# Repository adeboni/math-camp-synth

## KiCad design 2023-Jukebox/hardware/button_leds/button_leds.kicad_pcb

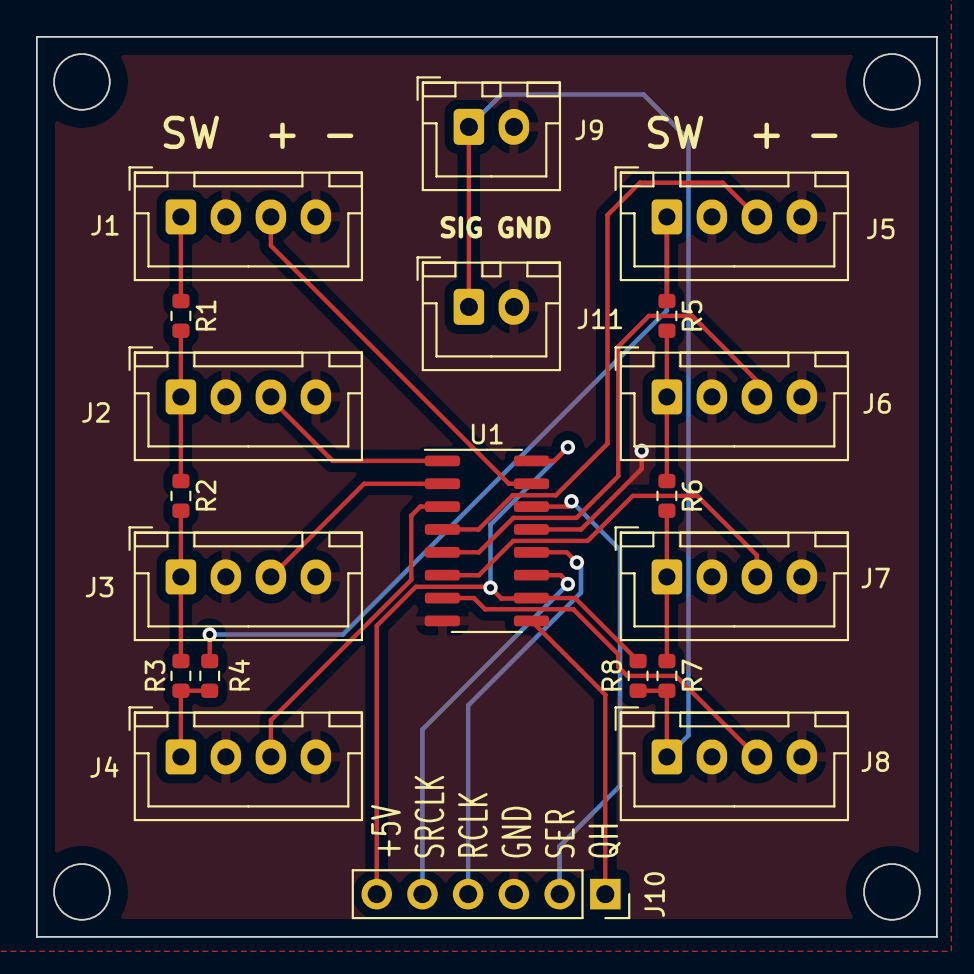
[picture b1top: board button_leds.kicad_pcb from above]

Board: 2 copper layers, 50.0 x 50.0 mm, 20 parts (0 on the bottom side), 22 nets.

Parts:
J1, J2, J3, J4, J5, J6, J7, J8: Conn_01x04; JST_XH_B4B-XH-A_1x04_P2.50mm_Vertical
J9, J11: JST_XH; JST_XH_B2B-XH-A_1x02_P2.50mm_Vertical
J10: Conn_01x06; PinSocket_1x06_P2.54mm_Vertical
R1, R2, R3, R4, R5, R6, R7, R8: 1k; R_0603_1608Metric
U1: 74HC595; SOIC-16_3.9x9.9mm_P1.27mm

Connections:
+5V: J10.6, R8.2, U1.10 (~SRCLR), U1.16 (VCC)
A1: J8.1, J9.1, J11.1, R7.2, R8.1
B1: J1.3, U1.15 (QA)
B2: J2.3, U1.1 (QB)
B3: J3.3, U1.2 (QC)
B4: J4.3, U1.3 (QD)
B5: J5.3, U1.4 (QE)
B6: J6.3, U1.5 (QF)
B7: J7.3, U1.6 (QG)
B8: J8.3, U1.7 (QH)
GND: J1.2, J1.4, J2.2, J2.4, J3.2, J3.4, J4.2, J4.4, J5.2, J5.4, J6.2, J6.4, J7.2, J7.4, J8.2, J8.4, J9.2, J10.3, J11.2, U1.8 (GND), U1.13 (~OE)
unnamed: J1.1, R1.1
unnamed: J2.1, R1.2, R2.1
unnamed: J3.1, R2.2, R3.1
unnamed: J4.1, R3.2, R4.1
unnamed: J5.1, R4.2, R5.1
unnamed: J6.1, R5.2, R6.1
unnamed: J7.1, R6.2, R7.1
QH: J10.1, U1.9 (QH')
RCLK: J10.4, U1.12 (RCLK)
SER: J10.2, U1.14 (SER)
SRCLK: J10.5, U1.11 (SRCLK)

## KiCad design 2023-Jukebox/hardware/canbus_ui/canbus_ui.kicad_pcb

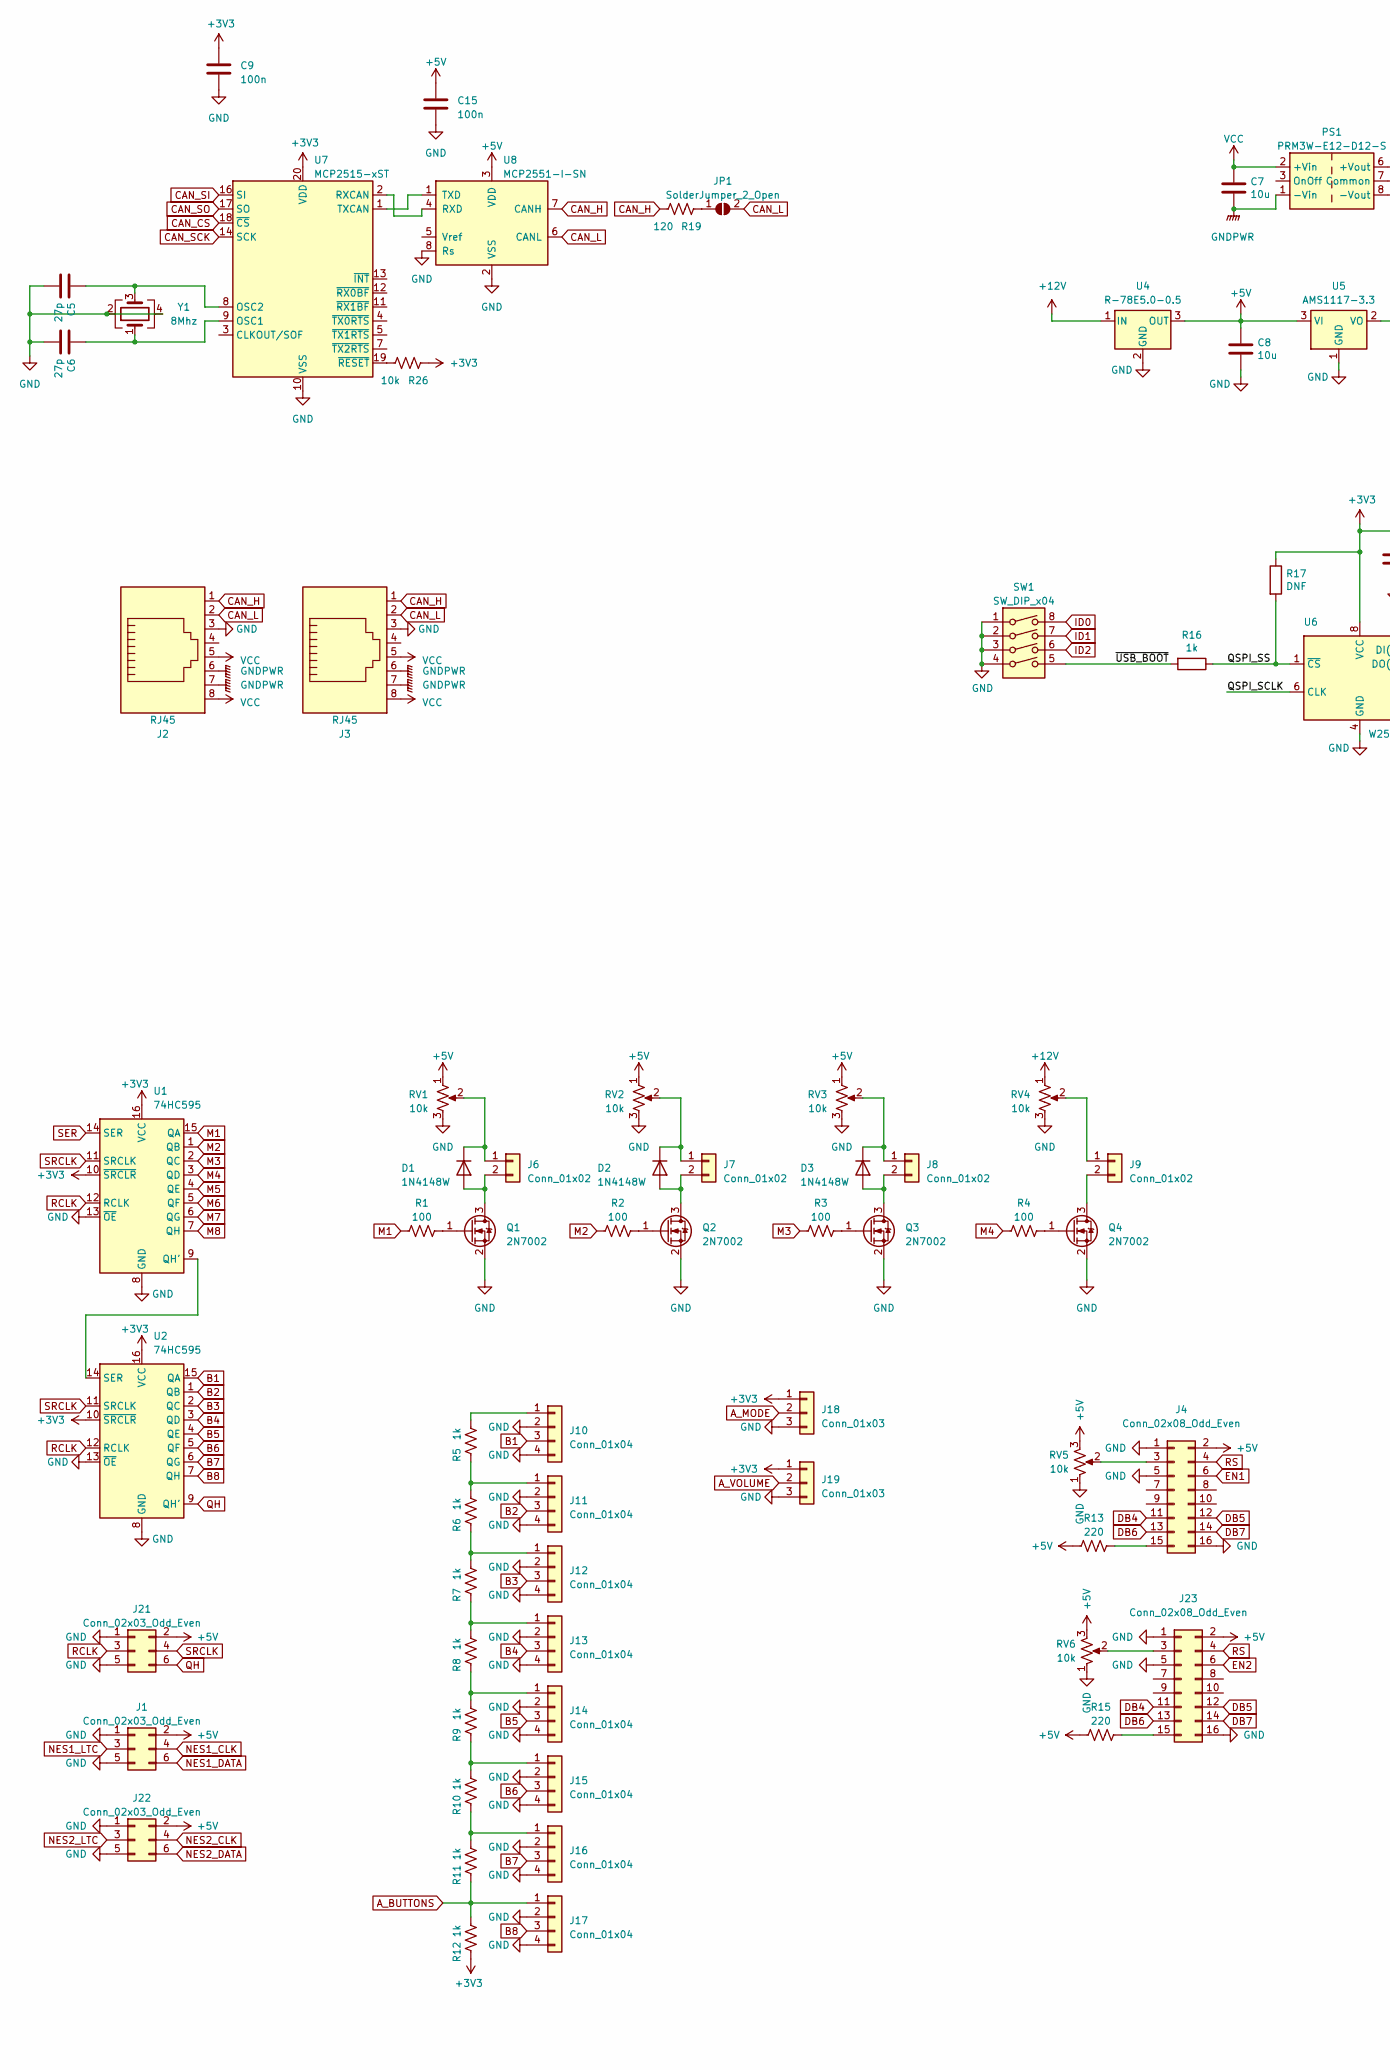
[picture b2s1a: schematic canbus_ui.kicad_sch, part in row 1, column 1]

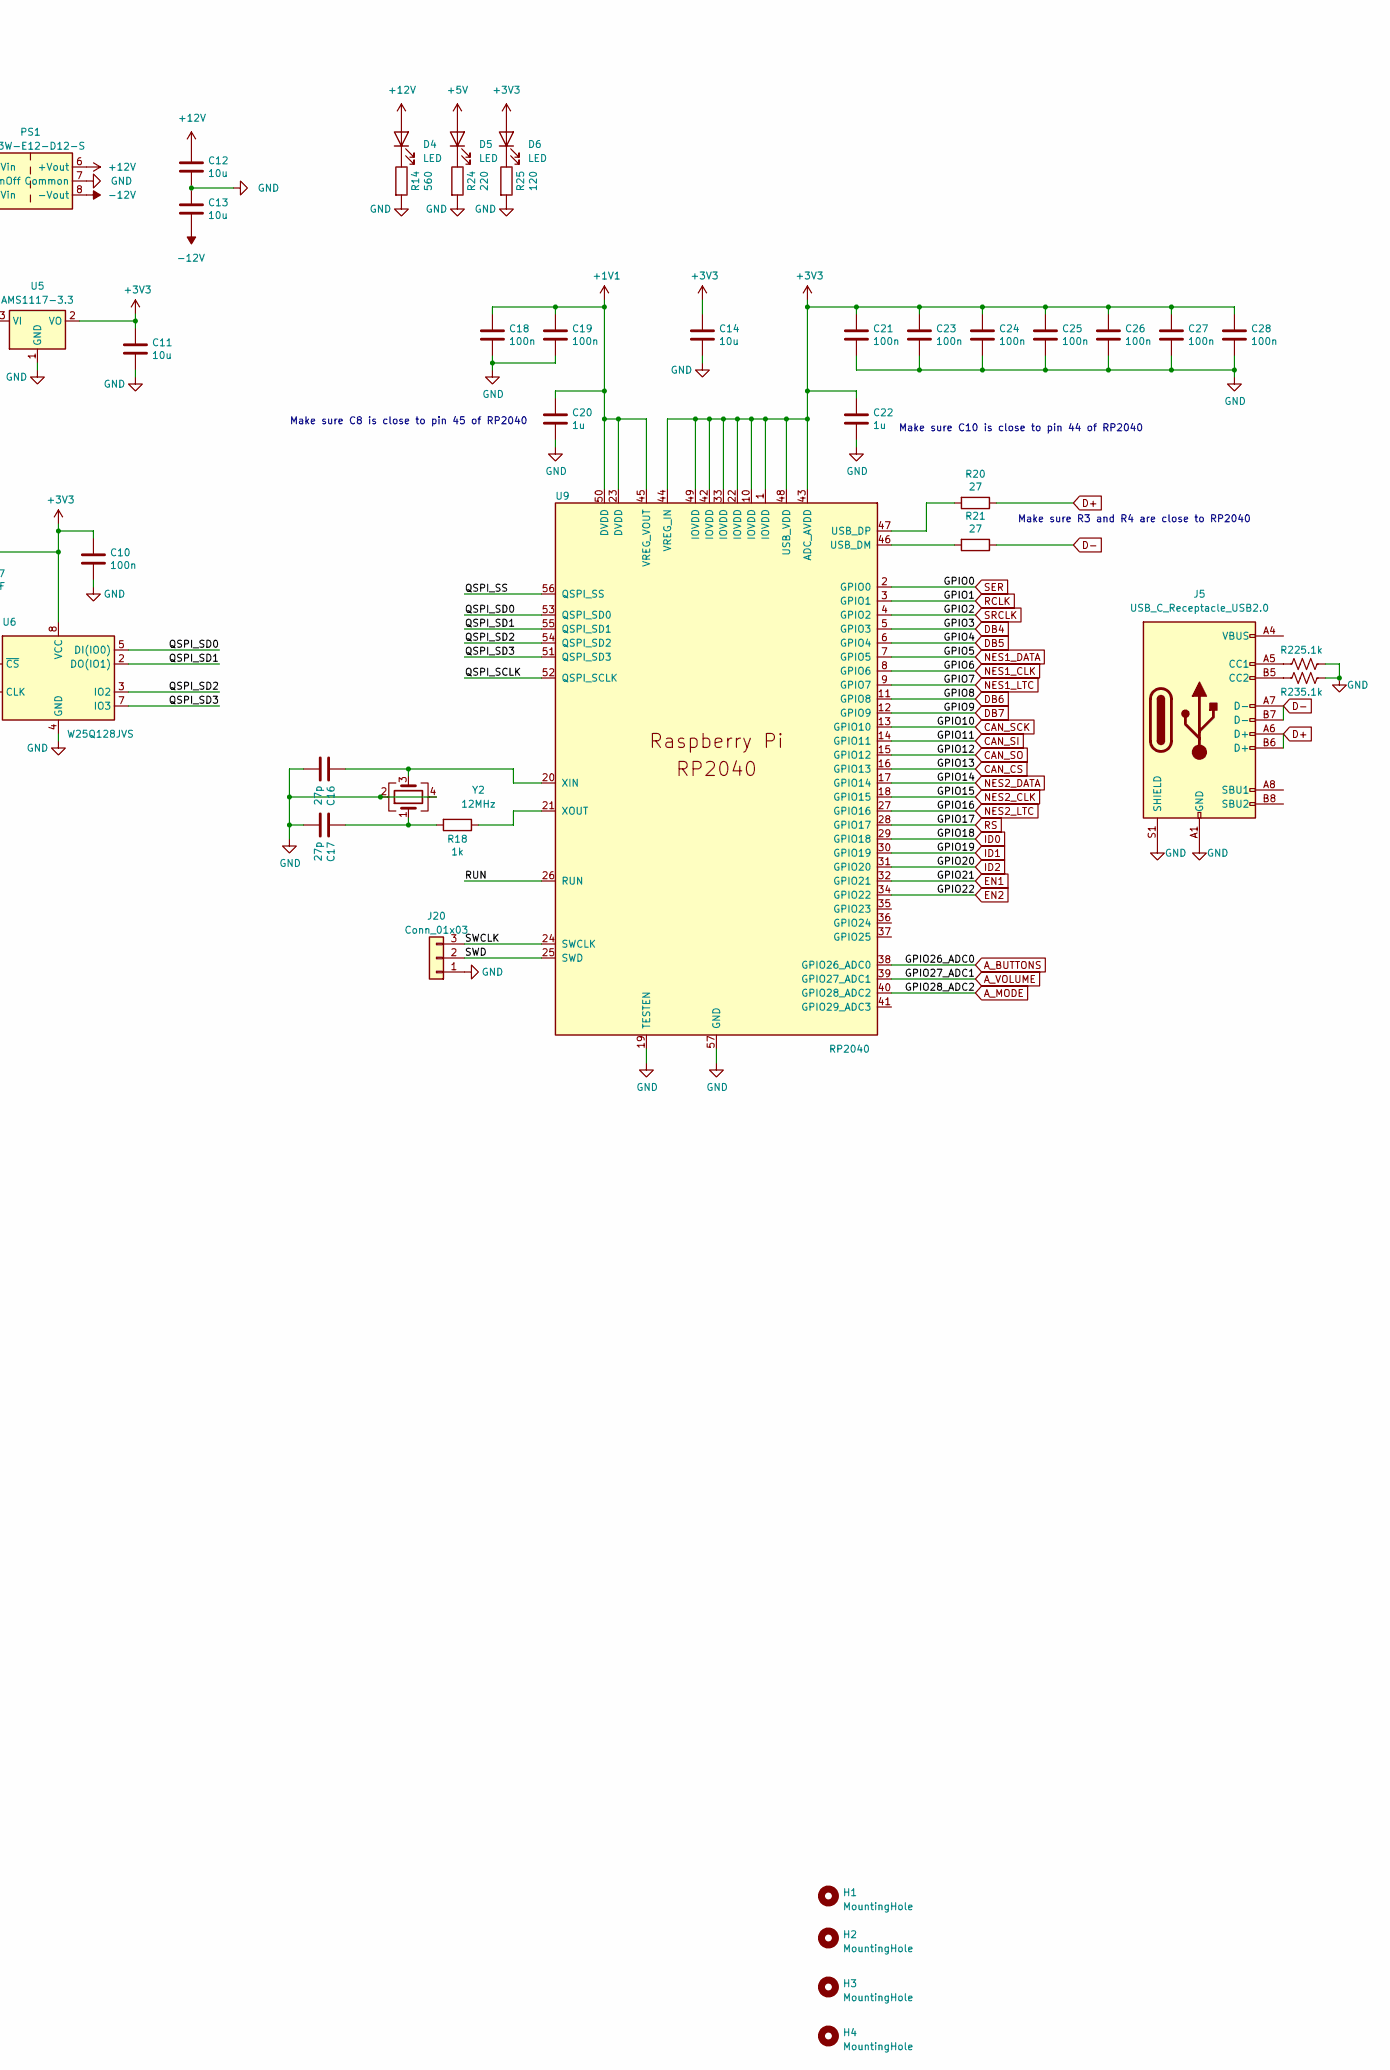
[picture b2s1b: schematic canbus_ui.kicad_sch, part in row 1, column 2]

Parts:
C5, C6, C16, C17: 27p; C_0603_1608Metric
C7, C8, C11, C12, C13, C14: 10u; C_0603_1608Metric
C9, C10, C15, C18, C19, C21, C23, C24, C25, C26, C27, C28: 100n; C_0603_1608Metric
C20, C22: 1u; C_0603_1608Metric
D1, D2, D3: 1N4148W; D_SOD-123
D4, D5, D6: LED; LED_0603_1608Metric
H1, H2, H3, H4: MountingHole; MountingHole_3.2mm_M3
J1, J21, J22: Conn_02x03_Odd_Even; IDC-Header_2x03_P2.54mm_Vertical
J2, J3: RJ45; RJ45_Amphenol_54602-x08_Horizontal
J4, J23: Conn_02x08_Odd_Even; IDC-Header_2x08_P2.54mm_Vertical
J5: USB_C_Receptacle_USB2.0; USB_C_Receptacle_Palconn_UTC16-G
J6, J7, J8, J9: Conn_01x02; JST_XH_B2B-XH-A_1x02_P2.50mm_Vertical
J10, J11, J12, J13, J14, J15, J16, J17: Conn_01x04; JST_XH_B4B-XH-A_1x04_P2.50mm_Vertical
J18, J19: Conn_01x03; JST_XH_B3B-XH-A_1x03_P2.50mm_Vertical
J20: Conn_01x03; PinHeader_1x03_P2.54mm_Vertical
JP1: SolderJumper_2_Open; SolderJumper-2_P1.3mm_Open_RoundedPad1.0x1.5mm
PS1: PRM3W-E12-D12-S; Converter_DCDC_XP_POWER-ITxxxxxS_THT
Q1, Q2, Q3, Q4: 2N7002; SOT-23
R1, R2, R3, R4: 100; R_0603_1608Metric
R5, R6, R7, R8, R9, R10, R11, R12, R16, R18: 1k; R_0603_1608Metric
R13, R15, R24: 220; R_0603_1608Metric
R14: 560; R_0603_1608Metric
R17: DNF; R_0603_1608Metric
R19, R25: 120; R_0603_1608Metric
R20, R21: 27; R_0603_1608Metric
R22, R23: 5.1k; R_0603_1608Metric
R26: 10k; R_0603_1608Metric
RV1, RV2, RV3, RV4, RV5, RV6: 10k; Potentiometer_Bourns_3386P_Vertical
SW1: SW_DIP_x04; SW_DIP_SPSTx04_Slide_Omron_A6S-410x_W8.9mm_P2.54mm
U1, U2: 74HC595; SOIC-16_3.9x9.9mm_P1.27mm
U4: R-78E5.0-0.5; Converter_DCDC_RECOM_R-78E-0.5_THT
U5: AMS1117-3.3; SOT-223-3_TabPin2
U6: W25Q128JVS; SOIC-8_5.23x5.23mm_P1.27mm
U7: MCP2515-xST; TSSOP-20_4.4x6.5mm_P0.65mm
U8: MCP2551-I-SN; SOIC-8_3.9x4.9mm_P1.27mm
U9: RP2040; QFN-56-1EP_7x7mm_P0.4mm_EP3.2x3.2mm
Y1: 8Mhz; Crystal_SMD_3225-4Pin_3.2x2.5mm
Y2: 12MHz; Crystal_SMD_3225-4Pin_3.2x2.5mm

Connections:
+1V1: C18.1, C19.1, C20.1, U9.23 (DVDD), U9.45 (VREG_VOUT), U9.50 (DVDD)
+3V3: C9.1, C10.1, C11.1, C14.1, C21.1, C22.1, C23.1, C24.1, C25.1, C26.1, C27.1, C28.1, D6.2 (A), J18.1, J19.1, R12.2, R17.1, R26.1, U1.10 (~SRCLR), U1.16 (VCC), U2.10 (~SRCLR), U2.16 (VCC), U5.2 (VO), U6.8 (VCC), U7.20 (VDD), U9.1 (IOVDD), U9.10 (IOVDD), U9.22 (IOVDD), U9.33 (IOVDD), U9.42 (IOVDD), U9.43 (ADC_AVDD), U9.44 (VREG_IN), U9.48 (USB_VDD), U9.49 (IOVDD)
+5V: C8.1, C15.1, D5.2 (A), J1.2, J4.2, J21.2, J22.2, J23.2, R13.1, R15.1, RV1.1, RV2.1, RV3.1, RV5.3, RV6.3, U4.3 (OUT), U5.3 (VI), U8.3 (VDD)
+12V: C12.1, D4.2 (A), PS1.6 (+Vout), RV4.1, U4.1 (IN)
-12V: C13.2, PS1.8 (-Vout)
/QSPI_SCLK: U6.6 (CLK), U9.52 (QSPI_SCLK)
/QSPI_SD0: U6.5 (DI(IO0)), U9.53 (QSPI_SD0)
/QSPI_SD1: U6.2 (DO(IO1)), U9.55 (QSPI_SD1)
/QSPI_SD2: U6.3 (IO2), U9.54 (QSPI_SD2)
/QSPI_SD3: U6.7 (IO3), U9.51 (QSPI_SD3)
/QSPI_SS: R16.1, R17.2, U6.1 (~CS), U9.56 (QSPI_SS)
/RUN: U9.26 (RUN)
/SWCLK: J20.3, U9.24 (SWCLK)
/SWD: J20.2, U9.25 (SWD)
/~USB_BOOT: R16.2, SW1.5
A_BUTTONS: J17.1, R11.2, R12.1, U9.38 (GPIO26_ADC0)
A_MODE: J18.2, U9.40 (GPIO28_ADC2)
A_VOLUME: J19.2, U9.39 (GPIO27_ADC1)
B1: J10.3, U2.15 (QA)
B2: J11.3, U2.1 (QB)
B3: J12.3, U2.2 (QC)
B4: J13.3, U2.3 (QD)
B5: J14.3, U2.4 (QE)
B6: J15.3, U2.5 (QF)
B7: J16.3, U2.6 (QG)
B8: J17.3, U2.7 (QH)
CAN_CS: U7.18 (~CS), U9.16 (GPIO13)
CAN_H: J2.1, J3.1, R19.2, U8.7 (CANH)
CAN_L: J2.2, J3.2, JP1.2 (B), U8.6 (CANL)
CAN_SCK: U7.14 (SCK), U9.13 (GPIO10)
CAN_SI: U7.16 (SI), U9.14 (GPIO11)
CAN_SO: U7.17 (SO), U9.15 (GPIO12)
D+: J5.A6 (D+), J5.B6 (D+), R20.1
D-: J5.A7 (D-), J5.B7 (D-), R21.1
DB4: J4.11, J23.11, U9.5 (GPIO3)
DB5: J4.12, J23.12, U9.6 (GPIO4)
DB6: J4.13, J23.13, U9.11 (GPIO8)
DB7: J4.14, J23.14, U9.12 (GPIO9)
EN1: J4.6, U9.32 (GPIO21)
EN2: J23.6, U9.34 (GPIO22)
GND: C5.2, C6.2, C8.2, C9.2, C10.2, C11.2, C12.2, C13.1, C14.2, C15.2, C16.2, C17.2, C18.2, C19.2, C20.2, C21.2, C22.2, C23.2, C24.2, C25.2, C26.2, C27.2, C28.2, J1.1, J1.5, J2.3, J3.3, J4.1, J4.5, J4.16, J5.A1 (GND), J5.A12 (GND), J5.B1 (GND), J5.B12 (GND), J5.S1 (SHIELD), J10.2, J10.4, J11.2, J11.4, J12.2, J12.4, J13.2, J13.4, J14.2, J14.4, J15.2, J15.4, J16.2, J16.4, J17.2, J17.4, J18.3, J19.3, J20.1, J21.1, J21.5, J22.1, J22.5, J23.1, J23.5, J23.16, PS1.7 (Common), Q1.2 (S), Q2.2 (S), Q3.2 (S), Q4.2 (S), R14.2, R22.1, R23.1, R24.2, R25.2, RV1.3, RV2.3, RV3.3, RV4.3, RV5.1, RV6.1, SW1.1, SW1.2, SW1.3, SW1.4, U1.8 (GND), U1.13 (~OE), U2.8 (GND), U2.13 (~OE), U4.2 (GND), U5.1 (GND), U6.4 (GND), U7.10 (VSS), U8.2 (VSS), U8.8 (Rs), U9.19 (TESTEN), U9.57 (GND), Y1.2, Y1.4, Y2.2, Y2.4
GNDPWR: C7.2, J2.6, J2.7, J3.6, J3.7, PS1.1 (-Vin)
ID0: SW1.8, U9.29 (GPIO18)
ID1: SW1.7, U9.30 (GPIO19)
ID2: SW1.6, U9.31 (GPIO20)
M1: R1.1, U1.15 (QA)
M2: R2.1, U1.1 (QB)
M3: R3.1, U1.2 (QC)
M4: R4.1, U1.3 (QD)
M5: U1.4 (QE)
M6: U1.5 (QF)
M7: U1.6 (QG)
M8: U1.7 (QH)
NES1_CLK: J1.4, U9.8 (GPIO6)
NES1_DATA: J1.6, U9.7 (GPIO5)
NES1_LTC: J1.3, U9.9 (GPIO7)
NES2_CLK: J22.4, U9.18 (GPIO15)
NES2_DATA: J22.6, U9.17 (GPIO14)
NES2_LTC: J22.3, U9.27 (GPIO16)
unnamed: C17.1, R18.2, Y2.1
unnamed: D1.2 (A), J6.2, Q1.3 (D)
unnamed: D1.1 (K), J6.1, RV1.2
unnamed: D2.2 (A), J7.2, Q2.3 (D)
unnamed: D2.1 (K), J7.1, RV2.2
unnamed: D3.2 (A), J8.2, Q3.3 (D)
unnamed: D3.1 (K), J8.1, RV3.2
unnamed: D4.1 (K), R14.1
unnamed: D5.1 (K), R24.1
unnamed: D6.1 (K), R25.1
unnamed: J4.3, RV5.2
unnamed: J4.15, R13.2
unnamed: J5.A5 (CC1), R22.2
unnamed: J5.B5 (CC2), R23.2
unnamed: J5.A4 (VBUS), J5.A9 (VBUS), J5.B4 (VBUS), J5.B9 (VBUS)
unnamed: J9.1, RV4.2
unnamed: J9.2, Q4.3 (D)
unnamed: J10.1, R5.1
unnamed: J11.1, R5.2, R6.1
unnamed: J12.1, R6.2, R7.1
unnamed: J13.1, R7.2, R8.1
unnamed: J14.1, R8.2, R9.1
unnamed: J15.1, R9.2, R10.1
unnamed: J16.1, R10.2, R11.1
unnamed: J23.3, RV6.2
unnamed: J23.15, R15.2
unnamed: JP1.1 (A), R19.1
unnamed: Q1.1 (G), R1.2
unnamed: Q2.1 (G), R2.2
unnamed: Q3.1 (G), R3.2
unnamed: Q4.1 (G), R4.2
unnamed: U1.9 (QH'), U2.14 (SER)
unnamed: C6.1, U7.9 (OSC1), Y1.1
unnamed: C5.1, U7.8 (OSC2), Y1.3
unnamed: U7.2 (RXCAN), U8.4 (RXD)
unnamed: U7.1 (TXCAN), U8.1 (TXD)
unnamed: R26.2, U7.19 (~RESET)
unnamed: R21.2, U9.46 (USB_DM)
unnamed: R20.2, U9.47 (USB_DP)
unnamed: C16.1, U9.20 (XIN), Y2.3
unnamed: R18.1, U9.21 (XOUT)
QH: J21.6, U2.9 (QH')
RCLK: J21.3, U1.12 (RCLK), U2.12 (RCLK), U9.3 (GPIO1)
RS: J4.4, J23.4, U9.28 (GPIO17)
SER: U1.14 (SER), U9.2 (GPIO0)
SRCLK: J21.4, U1.11 (SRCLK), U2.11 (SRCLK), U9.4 (GPIO2)
VCC: C7.1, J2.5, J2.8, J3.5, J3.8, PS1.2 (+Vin)

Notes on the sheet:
Make sure C8 is close to pin 45 of RP2040
Make sure R3 and R4 are close to RP2040
Make sure C10 is close to pin 44 of RP2040

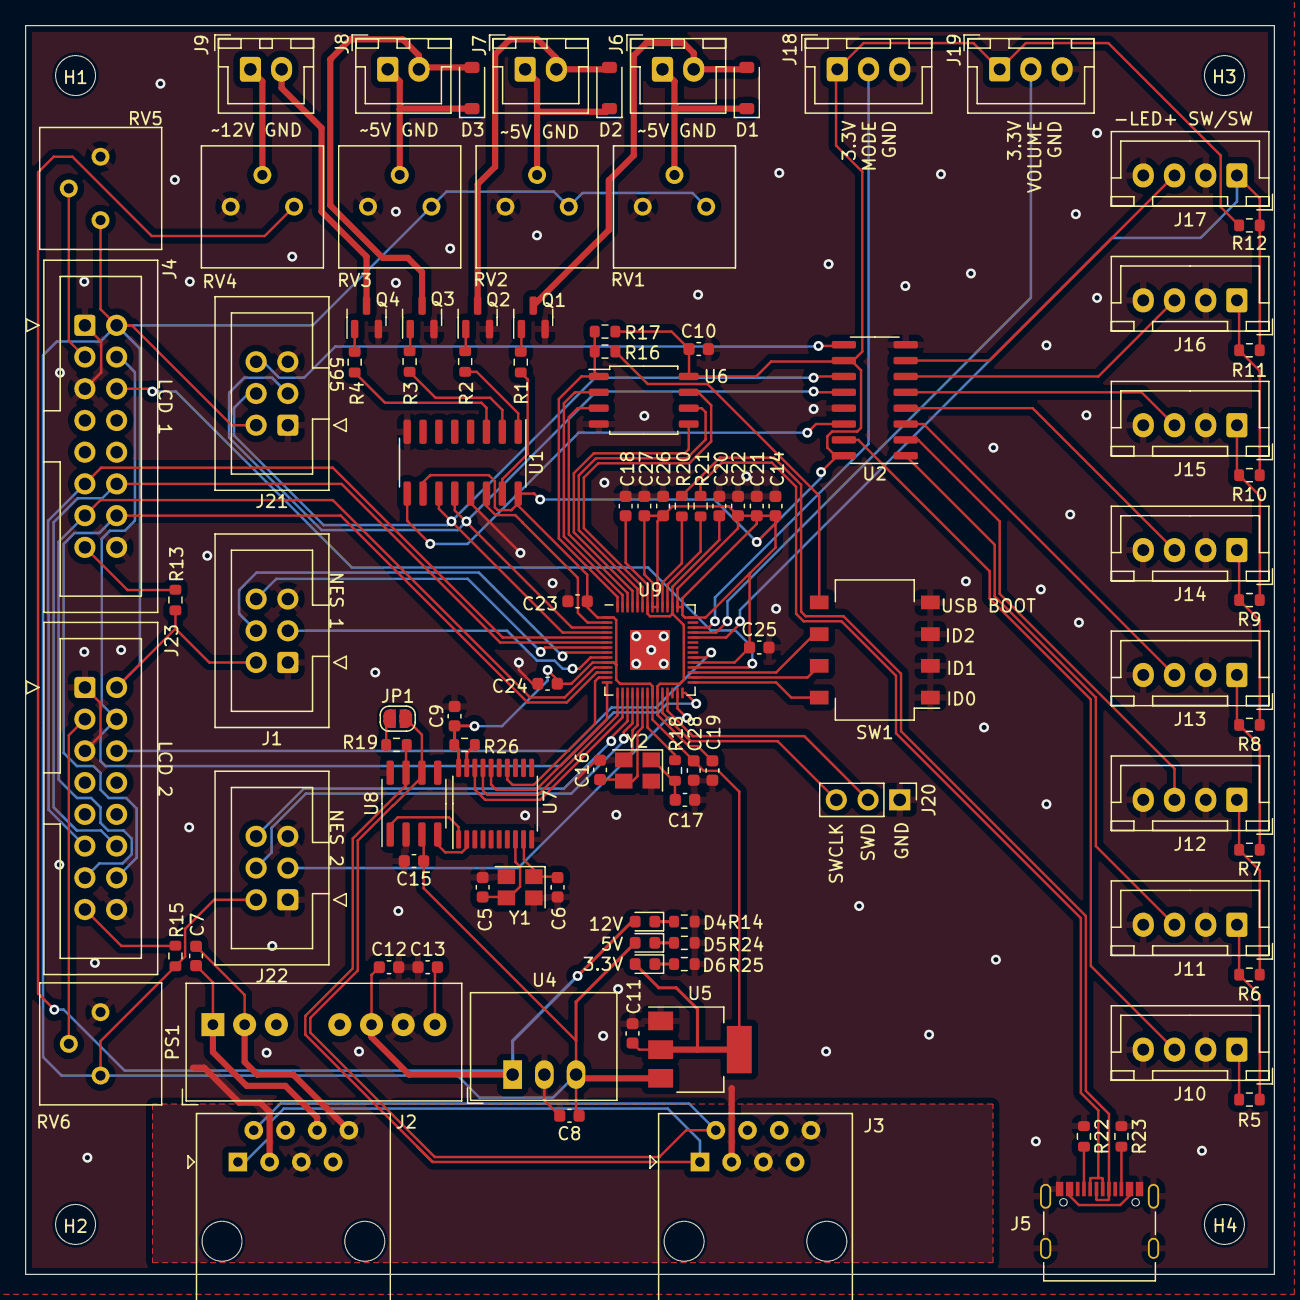
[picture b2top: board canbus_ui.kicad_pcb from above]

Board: 2 copper layers, 100.0 x 100.0 mm, 106 parts (0 on the bottom side), 101 nets.

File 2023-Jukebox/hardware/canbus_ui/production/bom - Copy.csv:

Designator,Footprint,Quantity,Value,LCSC Part #
"C10, C15, C18, C19, C21, C23, C24, C25, C26, C27, C28, C9",603,12,100n,C14663
"C11, C12, C13, C14, C7, C8",603,6,10u,C96446
"C16, C17, C5, C6",603,4,27p,C107045
"C20, C22",603,2,1u,C15849
"D1, D2, D3",D_SOD-123,3,1N4148W,C81598
"D4, D5, D6",603,3,LED,C2286
J5,USB_C_Receptacle_Palconn_UTC16-G,1,USB_C_Receptacle_USB2.0,C709357
"Q1, Q2, Q3, Q4",SOT-23,4,2N7002,C8545
"R1, R2, R3, R4",603,4,100,C22775
"R10, R11, R12, R16, R18, R5, R6, R7, R8, R9",603,10,1k,C21190
"R13, R15, R24",603,3,220,C22962
R14,603,1,560,C23204
"R19, R25",603,2,120,C22787
"R20, R21",603,2,27,C25190
"R22, R23",603,2,5.1k,C23186
R26,603,1,10k,C25804
SW1,SW_DIP_SPSTx04_Slide_Omron_A6S-410x_W8.9mm_P2.54mm,1,SW_DIP_x04,C306873
"U1, U2",SOIC-16_3.9x9.9mm_P1.27mm,2,74HC595,C5947
U5,SOT-223-3_TabPin2,1,AMS1117-3.3,C6186
U6,SOIC-8_5.23x5.23mm_P1.27mm,1,W25Q128JVS,C97521
U7,TSSOP-20_4.4x6.5mm_P0.65mm,1,MCP2515-xST,C15193
U8,SOIC-8_3.9x4.9mm_P1.27mm,1,MCP2551-I-SN,C7376
U9,QFN-56-1EP_7x7mm_P0.4mm_EP3.2x3.2mm,1,RP2040,C2040
Y1,Crystal_SMD_3225-4Pin_3.2x2.5mm,1,8Mhz,C2682774
Y2,Crystal_SMD_3225-4Pin_3.2x2.5mm,1,12MHz,C9002

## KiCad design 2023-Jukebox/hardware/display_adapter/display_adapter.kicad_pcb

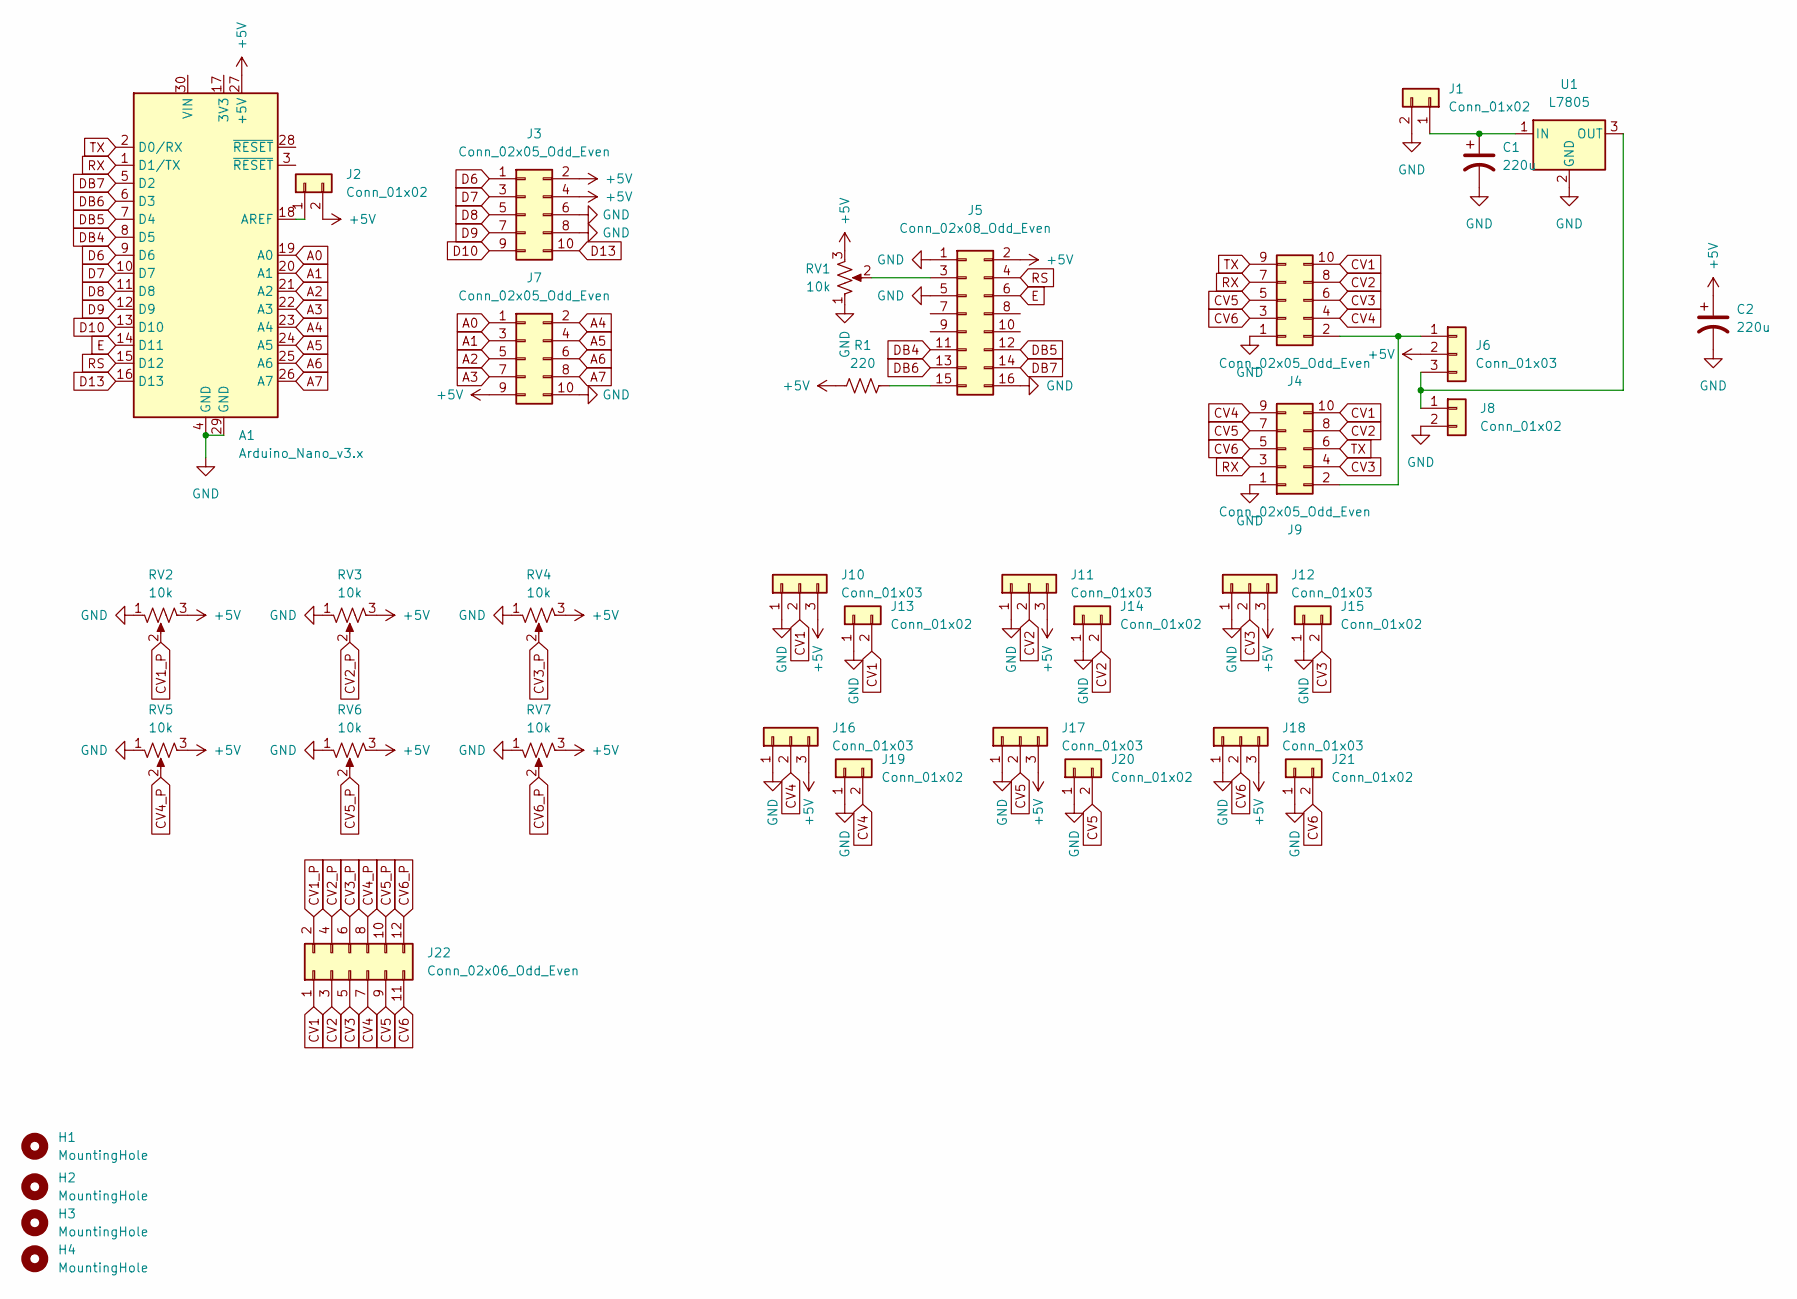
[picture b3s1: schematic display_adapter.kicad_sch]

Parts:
A1: Arduino_Nano_v3.x; Arduino_Nano
C1, C2: 220u; CP_Radial_D10.0mm_P5.00mm
H1, H2, H3, H4: MountingHole; MountingHole_3.2mm_M3
J1, J8, J13, J14, J15, J19, J20, J21: Conn_01x02; JST_XH_B2B-XH-A_1x02_P2.50mm_Vertical
J2: Conn_01x02; PinHeader_1x02_P2.54mm_Vertical
J3, J7: Conn_02x05_Odd_Even; PinHeader_2x05_P2.54mm_Vertical
J4, J9: Conn_02x05_Odd_Even; IDC-Header_2x05_P2.54mm_Vertical
J5: Conn_02x08_Odd_Even; IDC-Header_2x08_P2.54mm_Vertical
J6: Conn_01x03; PinHeader_1x03_P2.54mm_Vertical
J10, J11, J12, J16, J17, J18: Conn_01x03; JST_XH_B3B-XH-A_1x03_P2.50mm_Vertical
J22: Conn_02x06_Odd_Even; PinHeader_2x06_P2.54mm_Vertical
R1: 220; R_Axial_DIN0207_L6.3mm_D2.5mm_P10.16mm_Horizontal
RV1, RV2, RV3, RV4, RV5, RV6, RV7: 10k; Potentiometer_Bourns_3386P_Vertical
U1: L7805; TO-220-3_Horizontal_TabDown

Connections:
+5V: A1.27 (+5V), C2.1, J2.2, J3.2, J3.4, J5.2, J6.2, J7.9, J10.3, J11.3, J12.3, J16.3, J17.3, J18.3, R1.1, RV1.3, RV2.3, RV3.3, RV4.3, RV5.3, RV6.3, RV7.3
A0: A1.19 (A0), J7.1
A1: A1.20 (A1), J7.3
A2: A1.21 (A2), J7.5
A3: A1.22 (A3), J7.7
A4: A1.23 (A4), J7.2
A5: A1.24 (A5), J7.4
A6: A1.25 (A6), J7.6
A7: A1.26 (A7), J7.8
CV1: J4.10, J9.10, J10.2, J13.2, J22.1
CV1_P: J22.2, RV2.2
CV2: J4.8, J9.8, J11.2, J14.2, J22.3
CV2_P: J22.4, RV3.2
CV3: J4.6, J9.4, J12.2, J15.2, J22.5
CV3_P: J22.6, RV4.2
CV4: J4.4, J9.9, J16.2, J19.2, J22.7
CV4_P: J22.8, RV5.2
CV5: J4.5, J9.7, J17.2, J20.2, J22.9
CV5_P: J22.10, RV6.2
CV6: J4.3, J9.5, J18.2, J21.2, J22.11
CV6_P: J22.12, RV7.2
D6: A1.9 (D6), J3.1
D7: A1.10 (D7), J3.3
D8: A1.11 (D8), J3.5
D9: A1.12 (D9), J3.7
D10: A1.13 (D10), J3.9
D13: A1.16 (D13), J3.10
DB4: A1.8 (D5), J5.11
DB5: A1.7 (D4), J5.12
DB6: A1.6 (D3), J5.13
DB7: A1.5 (D2), J5.14
E: A1.14 (D11), J5.6
GND: A1.4 (GND), A1.29 (GND), C1.2, C2.2, J1.2, J3.6, J3.8, J4.1, J5.1, J5.5, J5.16, J7.10, J8.2, J9.1, J10.1, J11.1, J12.1, J13.1, J14.1, J15.1, J16.1, J17.1, J18.1, J19.1, J20.1, J21.1, RV1.1, RV2.1, RV3.1, RV4.1, RV5.1, RV6.1, RV7.1, U1.2 (GND)
unnamed: A1.18 (AREF), J2.1
unnamed: C1.1, J1.1, U1.1 (IN)
unnamed: J4.2, J6.1, J9.2
unnamed: J5.3, RV1.2
unnamed: J5.15, R1.2
unnamed: J6.3, J8.1, U1.3 (OUT)
RS: A1.15 (D12), J5.4
RX: A1.1 (D1/TX), J4.7, J9.3
TX: A1.2 (D0/RX), J4.9, J9.6

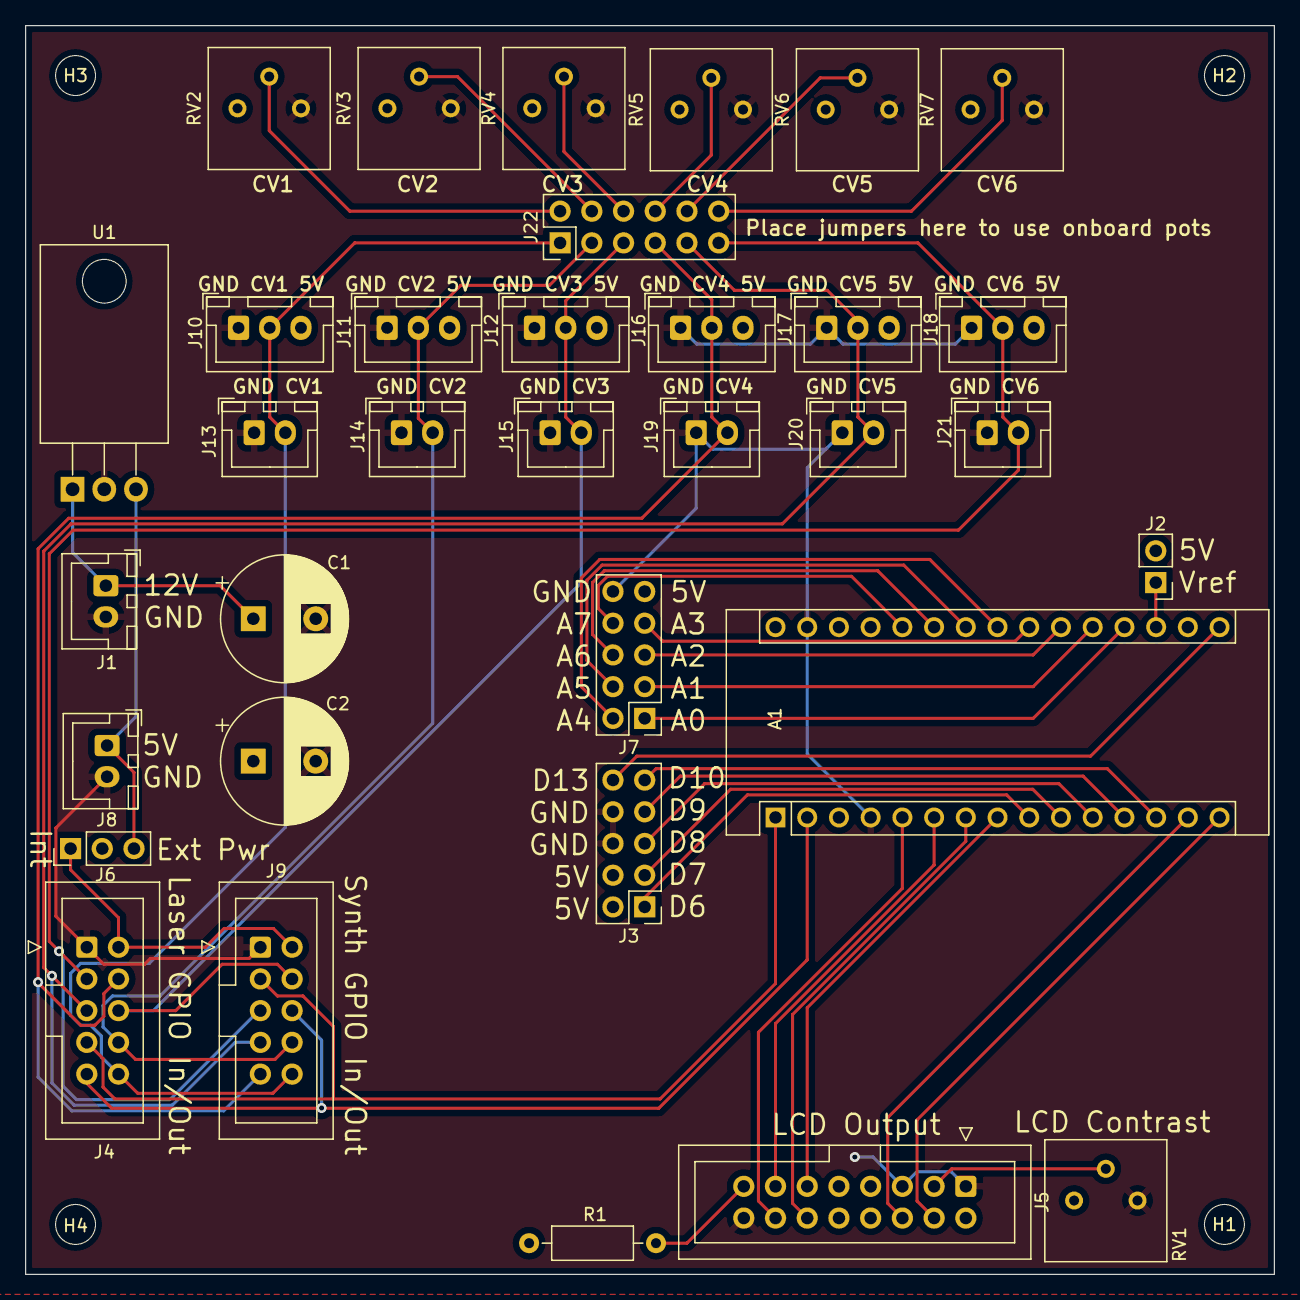
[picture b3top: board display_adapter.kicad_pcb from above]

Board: 2 copper layers, 100.0 x 100.0 mm, 38 parts (0 on the bottom side), 42 nets.

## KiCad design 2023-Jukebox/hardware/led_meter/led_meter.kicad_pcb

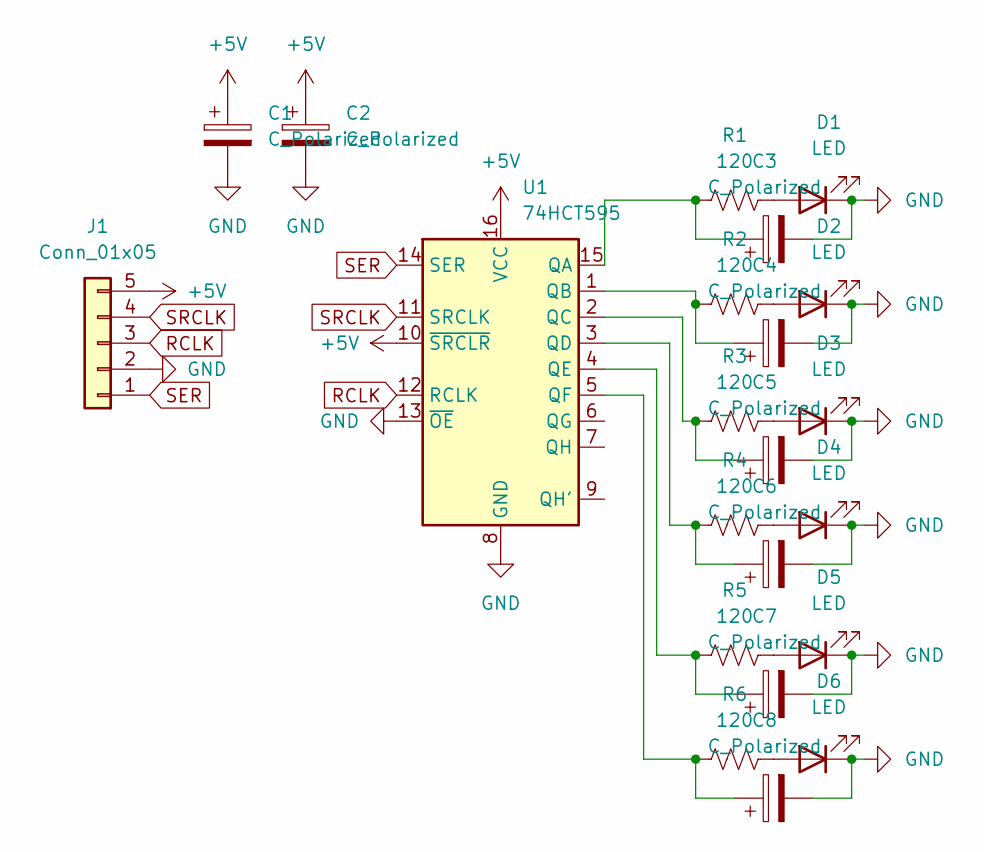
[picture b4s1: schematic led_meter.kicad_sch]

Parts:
C1, C2, C4, C5, C6, C7, C8: C_Polarized; CP_Radial_D6.3mm_P2.50mm
C3: C_Polarized
D1: LED
D2, D3, D4, D5, D6: LED; LED_D5.0mm_Clear
J1: Conn_01x05
R1: 120
R2, R3, R4, R5, R6: 120; R_Axial_DIN0207_L6.3mm_D2.5mm_P7.62mm_Horizontal
U1: 74HCT595

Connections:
+5V: C1.1, C2.1, J1.5, U1.10 (~SRCLR), U1.16 (VCC)
GND: C1.2, C2.2, C3.2, C4.2, C5.2, C6.2, C7.2, C8.2, D1.1 (K), D2.1 (K), D3.1 (K), D4.1 (K), D5.1 (K), D6.1 (K), J1.2, U1.8 (GND), U1.13 (~OE)
unnamed: C3.1, R1.1, U1.15 (QA)
unnamed: C4.1, R2.1, U1.1 (QB)
unnamed: C5.1, R3.1, U1.2 (QC)
unnamed: C6.1, R4.1, U1.3 (QD)
unnamed: C7.1, R5.1, U1.4 (QE)
unnamed: C8.1, R6.1, U1.5 (QF)
unnamed: D1.2 (A), R1.2
unnamed: D2.2 (A), R2.2
unnamed: D3.2 (A), R3.2
unnamed: D4.2 (A), R4.2
unnamed: D5.2 (A), R5.2
unnamed: D6.2 (A), R6.2
RCLK: J1.3, U1.12 (RCLK)
SER: J1.1, U1.14 (SER)
SRCLK: J1.4, U1.11 (SRCLK)

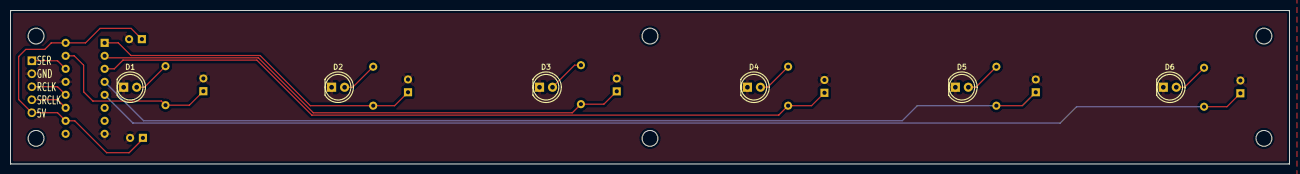
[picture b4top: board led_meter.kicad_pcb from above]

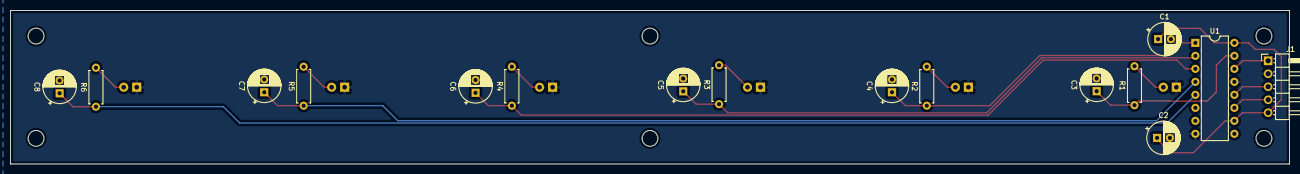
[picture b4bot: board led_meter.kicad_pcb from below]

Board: 2 copper layers, 250.0 x 30.0 mm, 22 parts (16 on the bottom side), 17 nets.
